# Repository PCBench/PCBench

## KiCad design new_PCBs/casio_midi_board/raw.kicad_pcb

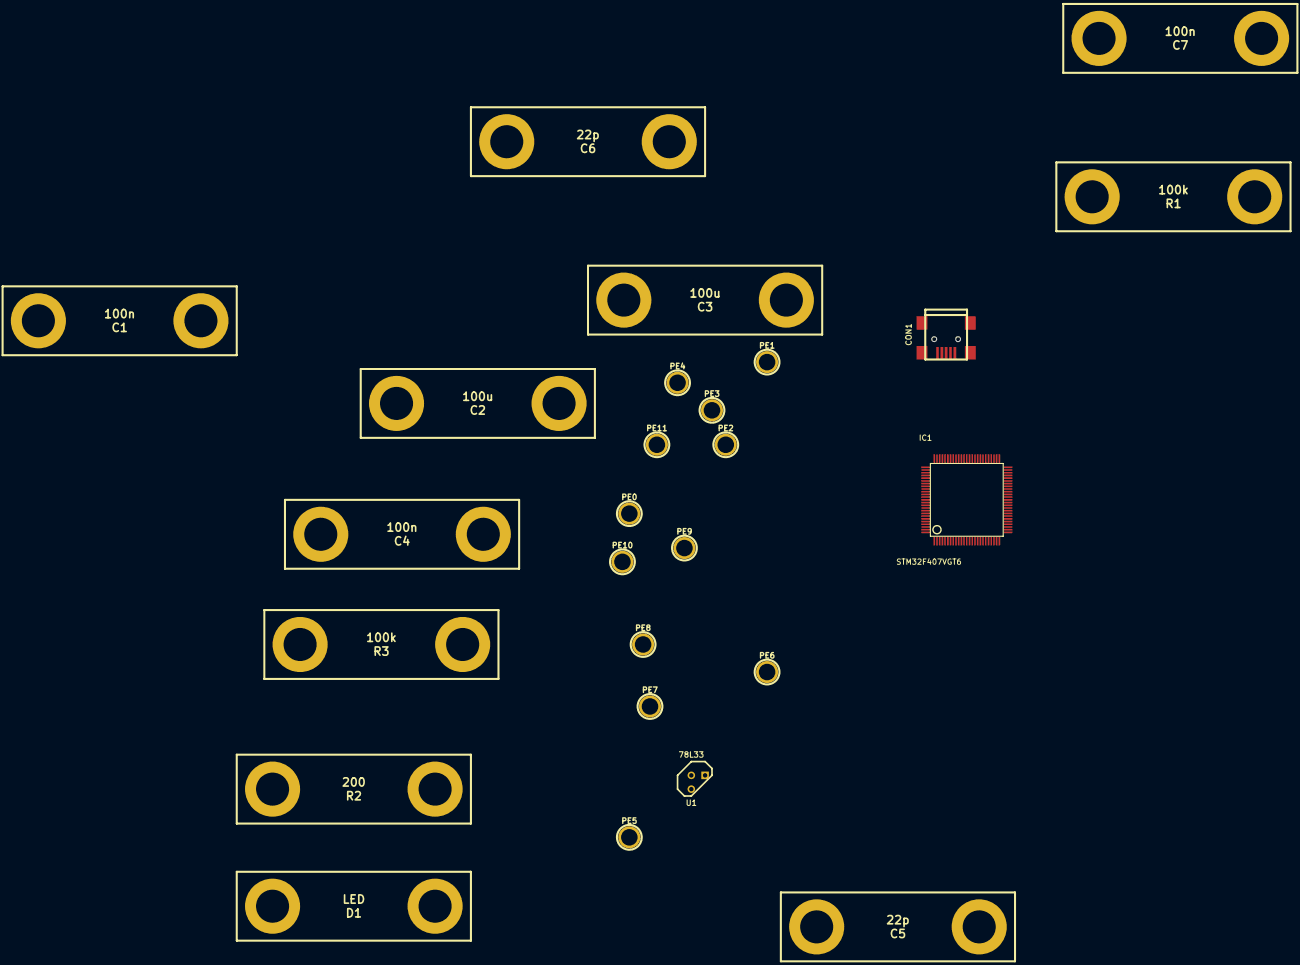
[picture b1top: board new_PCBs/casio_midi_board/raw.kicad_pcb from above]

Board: 2 copper layers, 26 parts (0 on the bottom side), 24 nets, no tracks yet.

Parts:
C1, C4, C7: 100n; 2PIN_6mm
C2, C3: 100u; 2PIN_6mm
C5, C6: 22p; 2PIN_6mm
CON1: USB-MINI-B; USB_MINI_B
D1: LED; 2PIN_6mm
IC1: STM32F407VGT6; QFP50P1600X1600X160-100N
PE0, PE1, PE2, PE3, PE4, PE5, PE6, PE7, PE8, PE9, PE10, PE11: CONN_1; 1pin
R1, R3: 100k; 2PIN_6mm
R2: 200; 2PIN_6mm
U1: 78L33; TO92

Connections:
GND: C1.2, C2.2, C3.2, C4.2, C5.2, C6.2, C7.2, CON1.5, D1.2, R3.2
unnamed: IC1.1, PE2.1
unnamed: IC1.23, R2.1
unnamed: D1.1, R2.2
unnamed: IC1.97, PE0.1
unnamed: IC1.98, PE1.1
unnamed: IC1.2, PE3.1
unnamed: IC1.3, PE4.1
unnamed: IC1.4, PE5.1
unnamed: IC1.5, PE6.1
unnamed: IC1.38, PE7.1
unnamed: IC1.39, PE8.1
unnamed: IC1.40, PE9.1
unnamed: IC1.41, PE10.1
unnamed: IC1.42, PE11.1
unnamed: C6.1, IC1.82
unnamed: C5.1, IC1.81
unnamed: C7.1, IC1.14, R1.1
unnamed: IC1.94, R3.1
unnamed: C1.1, C2.1, CON1.1
unnamed: C3.1, C4.1, IC1.6, IC1.11, IC1.19, IC1.28, IC1.50, IC1.75, IC1.100
unnamed: IC1.10, IC1.27, IC1.74, IC1.99
USB_DM: CON1.2, IC1.70
USB_DP: CON1.3, IC1.71

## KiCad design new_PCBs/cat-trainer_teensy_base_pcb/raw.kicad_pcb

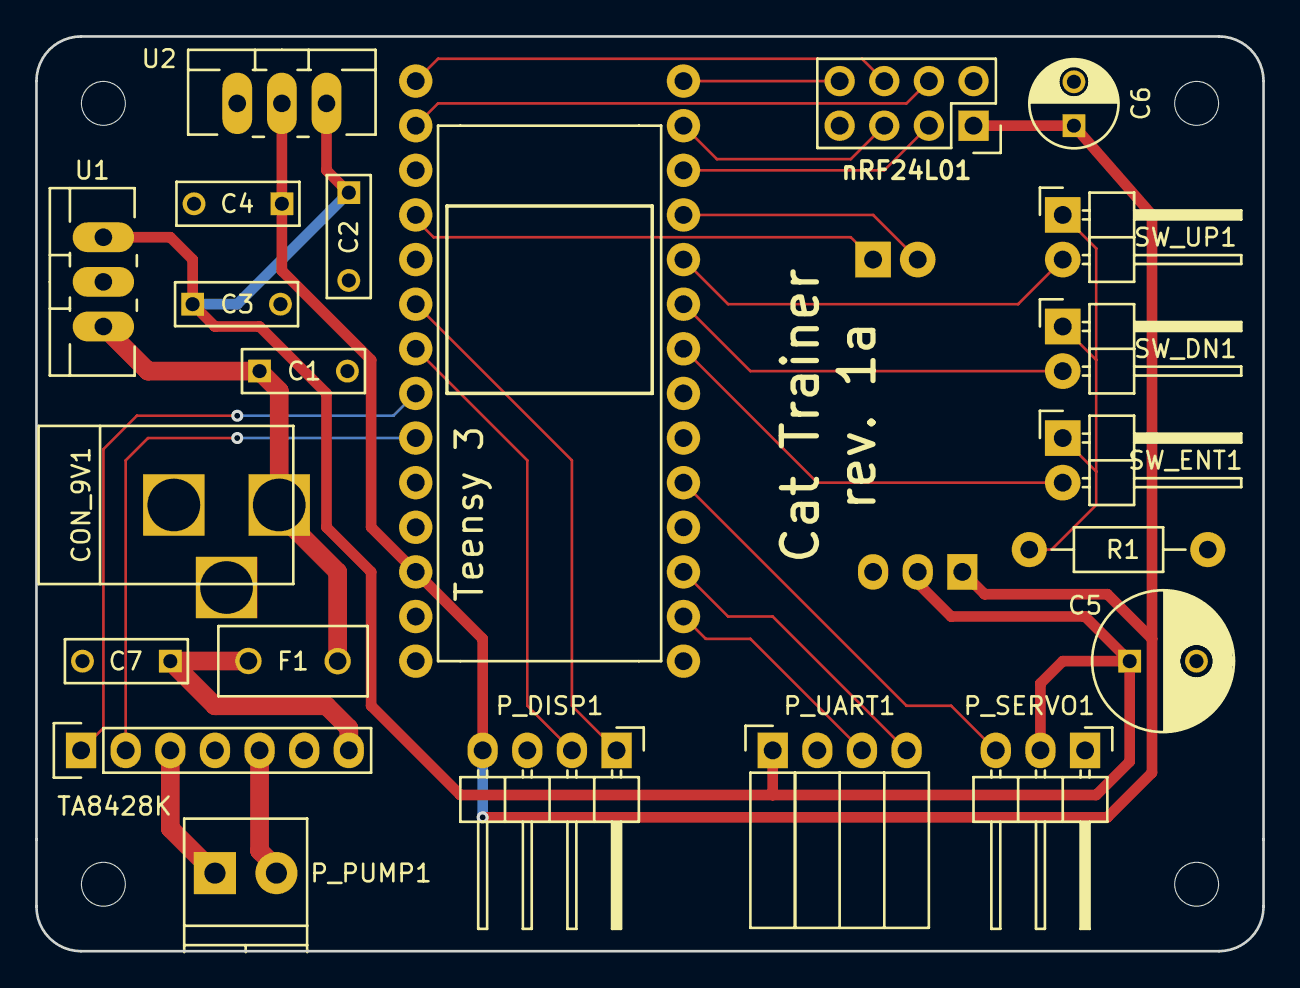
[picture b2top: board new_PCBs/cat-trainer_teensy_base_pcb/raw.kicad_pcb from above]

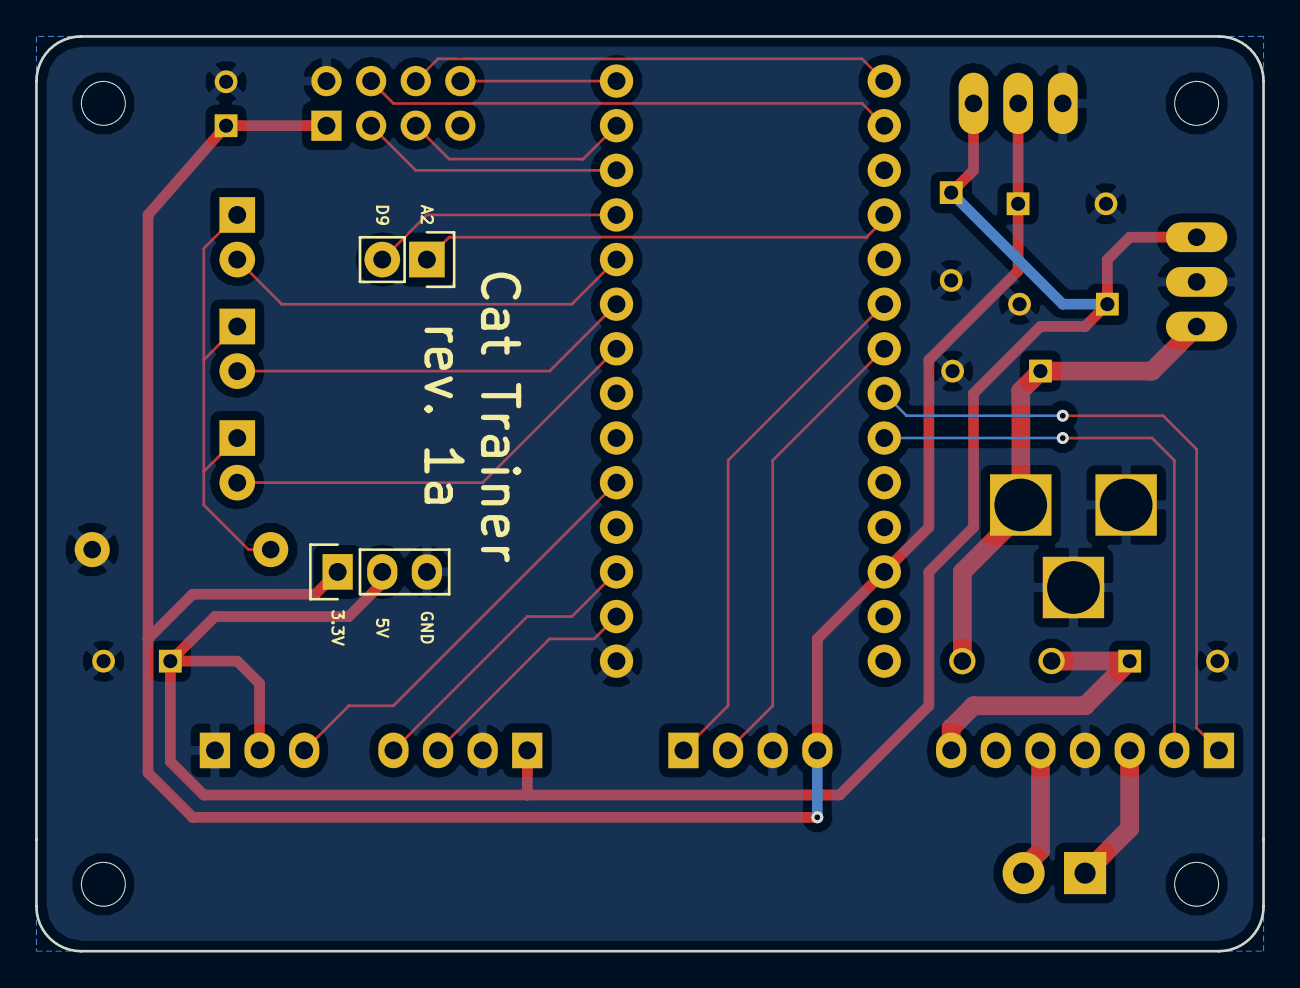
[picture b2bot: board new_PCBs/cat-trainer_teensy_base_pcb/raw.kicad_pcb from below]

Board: 2 copper layers, 69.9 x 52.1 mm, 24 parts (2 on the bottom side), 26 nets.

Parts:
C1: 330nF; C_Rect_L7_W2.5_P5
C2, C3: 100nF; C_Rect_L7_W2.5_P5
C4, C7: 10uF; C_Rect_L7_W2.5_P5
C5: 470uF; C_Radial_D8_L13_P3.8
C6: 100uF; C_Radial_D5_L11_P2.5
CON_9V1: BARREL_JACK
F1: F_Small; Fuse_TE5_Littlefuse-395Series
P_ACC1: CONN_01X03; Pin_Header_Straight_1x03
P_ACC2: CONN_01X02; Pin_Header_Straight_1x02
P_DISP1: CONN_01X04; Pin_Header_Angled_1x04
P_PUMP1: CONN_01X02; TerminalBlock_Pheonix_PT-3.5mm_2pol
P_SERVO1: CONN_01X03; Pin_Header_Angled_1x03
P_UART1: CONN_01X04; Socket_Strip_Angled_1x04
R1: 100; Resistor_Horizontal_RM10mm
SW_DN1: SW_PUSH; Pin_Header_Angled_1x02
SW_ENT1: SW_PUSH; Pin_Header_Angled_1x02
SW_UP1: SW_PUSH; Pin_Header_Angled_1x02
U1: LM7805CT; TO-220_Neutral123_Vertical_LargePads
U2: LD1117V33; TO-220_Neutral123_Vertical_LargePads
U3: Teensy_3.2; Teensy-3.1
U4: nRF24L01+; Socket_Strip_Straight_2x04
U5: TA8428K; Socket_Strip_Straight_1x07

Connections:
+3.3V: C4.1, C6.1, P_ACC1.1, P_DISP1.4, U2.2, U3.24, U4.2
+5V: C2.1, C3.1, C5.1, P_ACC1.2, P_SERVO1.2, P_UART1.1, U1.3, U2.3
+9V: C1.1, CON_9V1.1, F1.1, U1.1
ACC1: P_ACC2.2, U3.9
ACC2: P_ACC2.1, U3.16
GND: C1.2, C2.2, C3.2, C4.2, C5.2, C6.2, C7.2, CON_9V1.2, CON_9V1.3, P_ACC1.3, P_DISP1.3, P_SERVO1.1, P_UART1.2, R1.2, U1.2, U2.1, U3.27, U4.1, U5.4
NC: U3.2, U3.4, U3.5, U3.15, U3.17, U3.22, U3.23, U3.25, U3.26, U4.8
unnamed: C7.1, F1.2, U5.7
unnamed: P_DISP1.1, U3.18
unnamed: P_DISP1.2, U3.19
unnamed: P_PUMP1.1, U5.3
unnamed: P_PUMP1.2, U5.5
unnamed: P_SERVO1.3, U3.3
unnamed: P_UART1.3, U3.0
unnamed: P_UART1.4, U3.1
unnamed: R1.1, SW_DN1.1, SW_ENT1.1, SW_UP1.1
unnamed: SW_DN1.2, U3.7
unnamed: SW_ENT1.2, U3.6
unnamed: SW_UP1.2, U3.8
unnamed: U3.10, U4.4
unnamed: U3.11, U4.6
unnamed: U3.12, U4.7
unnamed: U3.13, U4.5
unnamed: U3.14, U4.3
unnamed: U3.20, U5.1
unnamed: U3.21, U5.2

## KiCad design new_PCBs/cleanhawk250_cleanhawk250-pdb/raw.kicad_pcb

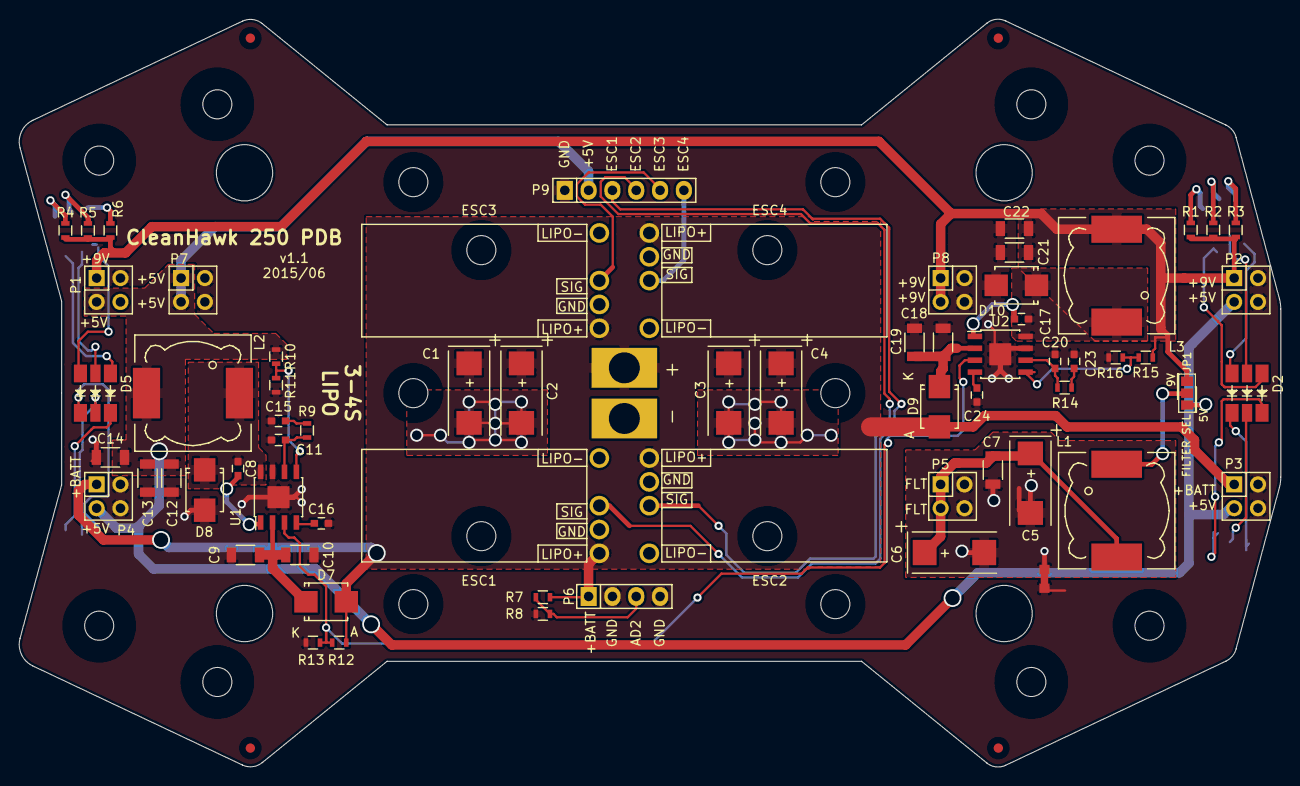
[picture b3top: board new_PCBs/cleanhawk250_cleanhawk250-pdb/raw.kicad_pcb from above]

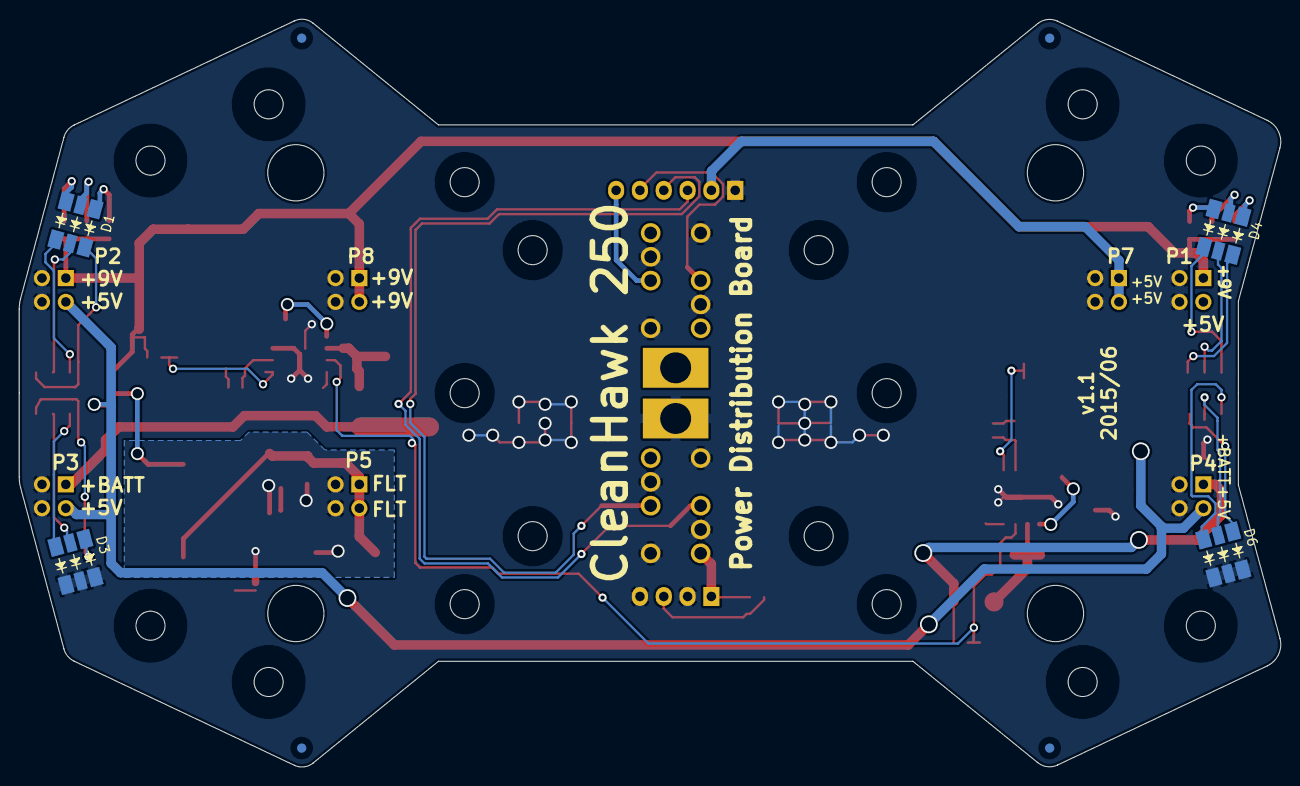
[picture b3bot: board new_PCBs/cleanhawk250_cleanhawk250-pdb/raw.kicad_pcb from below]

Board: 2 copper layers, 134.5 x 79.7 mm, 80 parts (8 on the bottom side), 45 nets.

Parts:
C1, C2, C3, C4: 33uF/25V/np; TantalC_SizeD_EIA-7343_Reflow
C5, C6: 100uF/16V; TantalC_SizeD_EIA-7343_Reflow
C7, C9, C10, C18, C19: 10uF/35V; C_1206
C8, C17: 100nF; C_0603
C11, C20: 18pF; C_0603
C12, C13, C14: 22uF/10V; C_1206
C15, C23: 680pF; C_0603
C16, C24: 8.2nF; C_0603
C21, C22: 22uF/16V; C_1206
D1, D2, D3, D4, D5, D6: RGB_LED_5050; LED_5050_RGB
D7, D8, D9, D10: B340LB; Diode-SMB_Standard
ESC1, ESC2, ESC3, ESC4: KISS_ESC_18A; Kiss_ESC_18A_v1.1
F1, F2, F3, F4, F5, F6, F7, F8: SPECIAL; FIDUCIAL_1MM
FRAME1: SPECIAL; Emax250_Bottom_Holes
JP1: FILTER SEL; AB2_SJMP_03-1
JP2: JUMPER; NetTie-I_Connected_SMD
L1: 820uH; Choke_SMD_12x12mm_h6mm
L2, L3: 8.2uH; Choke_SMD_12x12mm_h6mm
P1, P2, P3, P4, P5, P7, P8: CONN_02X02; Pin_Header_Straight_2x02
P6: CONN_01X04; Pin_Header_Straight_1x04
P9: CONN_01X06; Pin_Header_Straight_1x06
R1, R3: 68; R_0603
R2, R5: 120; R_0603
R4, R6: 68/np; R_0603
R7, R10, R15: 10k/1%; R_0603
R8: 2.32k/1%; R_0603
R9, R14: 78.7k; R_0603
R11: 1.91k/1%; R_0603
R12: 169k/np; R_0603
R13: 28k/np; R_0603
R16: 976/1%; R_0603
U1, U2: TPS54331; SOIC-8-1EP_3.9x4.9mm_Pitch1.27mm
W1: WIREPADS; WirePads_12AWG_TH

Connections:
+5V: C12.1, C13.1, C14.1, JP1.3, L2.2, P1.3, P2.3, P3.3, P4.3, P7.1, P7.3, P9.2, R10.1
+9V: C21.1, C22.1, JP1.1, L3.2, P1.1, P2.1, P8.1, P8.3, R1.2, R2.2, R3.2, R4.2, R5.2, R6.2, R15.1
+BATT: C1.1, C2.1, C3.1, C4.1, D7.2, D9.2, ESC1.1, ESC2.1, ESC3.1, ESC4.1, P3.1, P4.1, P6.1, R7.2, R12.1, W1.+
ESC1: ESC1.2, P9.3
ESC2: ESC2.2, P9.4
ESC3: ESC3.2, P9.5
ESC4: ESC4.2, P9.6
GND: C1.2, C2.2, C3.2, C4.2, C9.2, C10.2, C11.2, C12.2, C13.2, C14.2, C15.2, C16.2, C18.2, C19.2, C20.2, C21.2, C22.2, C23.2, C24.2, D3.4, D3.5, D3.6, D6.4, D6.5, D6.6, D8.2, D10.2, ESC1.3, ESC1.4, ESC2.3, ESC2.4, ESC3.3, ESC3.4, ESC4.3, ESC4.4, JP2.1, P1.2, P1.4, P2.2, P2.4, P3.2, P3.4, P4.2, P4.4, P6.2, P6.4, P7.2, P7.4, P8.2, P8.4, P9.1, R8.2, R11.2, R13.2, R16.2, U1.7, U1.9, U2.7, U2.9, W1.-
GNDA: C5.2, C6.2, C7.2, JP2.2, P5.2, P5.4
unnamed: C5.1, C6.1, C7.1, L1.2, P5.1, P5.3
unnamed: C8.1, U1.1
unnamed: C8.2, D8.1, L2.1, U1.8
unnamed: C9.1, C10.1, D7.1, U1.2
unnamed: C11.1, R9.1, U1.6
unnamed: C15.1, R9.2
unnamed: C16.1, U1.4
unnamed: C17.1, U2.1
unnamed: C17.2, D10.1, L3.1, U2.8
unnamed: C18.1, C19.1, D9.1, U2.2
unnamed: C20.1, R14.1, U2.6
unnamed: C23.1, R14.2
unnamed: C24.1, U2.4
unnamed: D1.1, R1.1
unnamed: D1.2, R2.1
unnamed: D1.3, R3.1
unnamed: D1.4, D2.3
unnamed: D1.5, D2.2
unnamed: D1.6, D2.1
unnamed: D2.4, D3.3
unnamed: D2.5, D3.2
unnamed: D2.6, D3.1
unnamed: D4.1, R4.1
unnamed: D4.2, R5.1
unnamed: D4.3, R6.1
unnamed: D4.4, D5.3
unnamed: D4.5, D5.2
unnamed: D4.6, D5.1
unnamed: D5.4, D6.3
unnamed: D5.5, D6.2
unnamed: D5.6, D6.1
unnamed: JP1.2, L1.1
unnamed: P6.3, R7.1, R8.1
unnamed: R10.2, R11.1, U1.5
unnamed: R15.2, R16.1, U2.5
REG_EN: R12.2, R13.1, U1.3, U2.3

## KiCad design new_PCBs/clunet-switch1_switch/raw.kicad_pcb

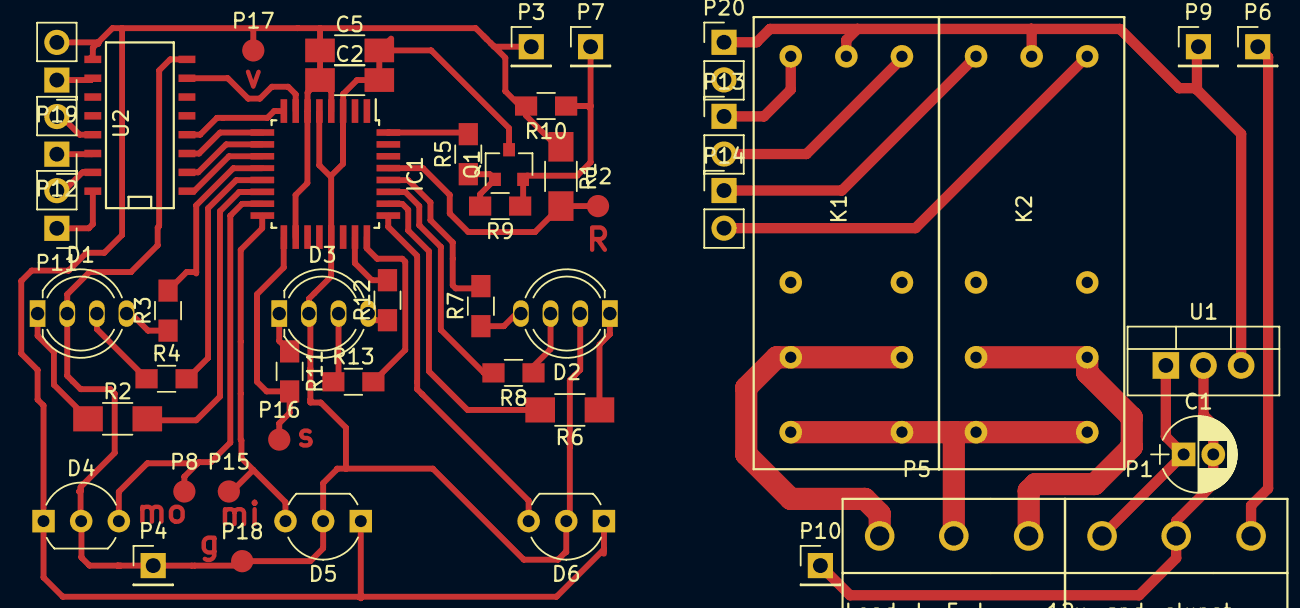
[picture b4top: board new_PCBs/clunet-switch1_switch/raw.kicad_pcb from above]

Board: 2 copper layers, 48 parts (0 on the bottom side), 48 nets.

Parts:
C1: 100mkf; CP_Radial_D5.0mm_P2.00mm
C2: 10mkf; C_1206_HandSoldering
C5: C_Small; C_1206_HandSoldering
D1, D2, D3: Led1; LED_D5.0mm-4-LL
D4, D5, D6: AH201; TO-92_Inline_Wide
IC1: ATMEGA8A-A; TQFP-32_7x7mm_Pitch0.8mm-LUT
K1, K2: RT424F05
P1: 12v-gnd-clunet; DG301-5.0-3x
P2: Reset; Measurement_Point_Round-SMD-Pad_Small
P3, P9: Vcc; Socket_Strip_Straight_1x01_Pitch2.54mm
P4, P10: Gnd; Socket_Strip_Straight_1x01_Pitch2.54mm
P5: Load-L-F-L; DG301-5.0-3x
P6, P7: Clunet; Socket_Strip_Straight_1x01_Pitch2.54mm
P8: CON_MOS; Measurement_Point_Round-SMD-Pad_Small
P11, P13: R1_; Socket_Strip_Straight_1x02_Pitch2.54mm
P12, P14: R2_; Socket_Strip_Straight_1x02_Pitch2.54mm
P15: CON_MIS; Measurement_Point_Round-SMD-Pad_Small
P16: CON_SCK; Measurement_Point_Round-SMD-Pad_Small
P17: Vcc_Prog; Measurement_Point_Round-SMD-Pad_Small
P18: Gnd_Prog; Measurement_Point_Round-SMD-Pad_Small
P19, P20: SPK; Socket_Strip_Straight_1x02_Pitch2.54mm
Q1: PNP BC858; SOT-23
R1: 1.5K; R_1206_HandSoldering
R2, R6: 470R; R_1206_HandSoldering
R3, R4, R7, R8, R11, R12, R13: 470R; R_0805_HandSoldering
R5: 2.2K; R_0805_HandSoldering
R9: 22K; R_0805_HandSoldering
R10: 560R; R_0805_HandSoldering
U1: 7805; TO-220_Vertical-LM7805
U2: ULN2003-norm; SO-16-N

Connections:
+5V: K1.3, K2.3, P9.1, P20.1, U1.VO
+12V: C1.1, P1.1, U1.VI
/LED1_1: IC1.14, R2.2
/LED1_2: IC1.13, R4.2
/LED1_3: IC1.12, R3.2
/LED2_1: IC1.17, P16.1, R11.2
/LED2_2: IC1.23, R12.2
/LED2_3: IC1.24, R13.2
/LED3_1: IC1.26, R6.2
/LED3_2: IC1.27, R8.2
/LED3_3: IC1.28, R7.2
/R1_1: IC1.11, U2.1
/R1_2: IC1.10, U2.2
/R2_1: IC1.9, U2.3
/R2_2: IC1.8, U2.4
/SW1: D4.3, IC1.15, P8.1
/SW2: D5.3, IC1.16, P15.1
/SW3: D6.3, IC1.25
/spk: IC1.7, U2.7
GND: C2.2, C5.2, D1.2, D2.2, D3.2, D4.2, D5.2, D6.2, IC1.3, IC1.5, IC1.21, P4.1, P18.1, Q1.3, U2.8
GNDA: C1.2, P1.2, P10.1, U1.GND
unnamed: D1.1, R2.1
unnamed: D1.3, R4.1
unnamed: D1.4, R3.1
unnamed: D2.1, R6.1
unnamed: D2.3, R8.1
unnamed: D2.4, R7.1
unnamed: D3.1, R11.1
unnamed: D3.3, R13.1
unnamed: D3.4, R12.1
unnamed: IC1.29, P2.1, R1.2
unnamed: IC1.32, R5.2
unnamed: K1.1, P13.2
unnamed: K1.2, P13.1
unnamed: K1.11, K1.21, P5.1
unnamed: K1.14, K1.24, K2.14, K2.24, P5.2
unnamed: K2.1, P14.2
unnamed: K2.2, P14.1
unnamed: K2.11, K2.21, P5.3
unnamed: P1.3, P6.1
unnamed: P11.1, U2.16
unnamed: P11.2, U2.15
unnamed: P12.1, U2.14
unnamed: P12.2, U2.13
unnamed: P19.1, U2.10
unnamed: Q1.1, R5.1, R9.2
VCC: C2.1, C5.1, D4.1, D5.1, D6.1, IC1.4, IC1.6, IC1.18, P3.1, P17.1, P19.2, R1.1, R10.2, U2.9
clunet: P7.1, Q1.2, R9.1, R10.1

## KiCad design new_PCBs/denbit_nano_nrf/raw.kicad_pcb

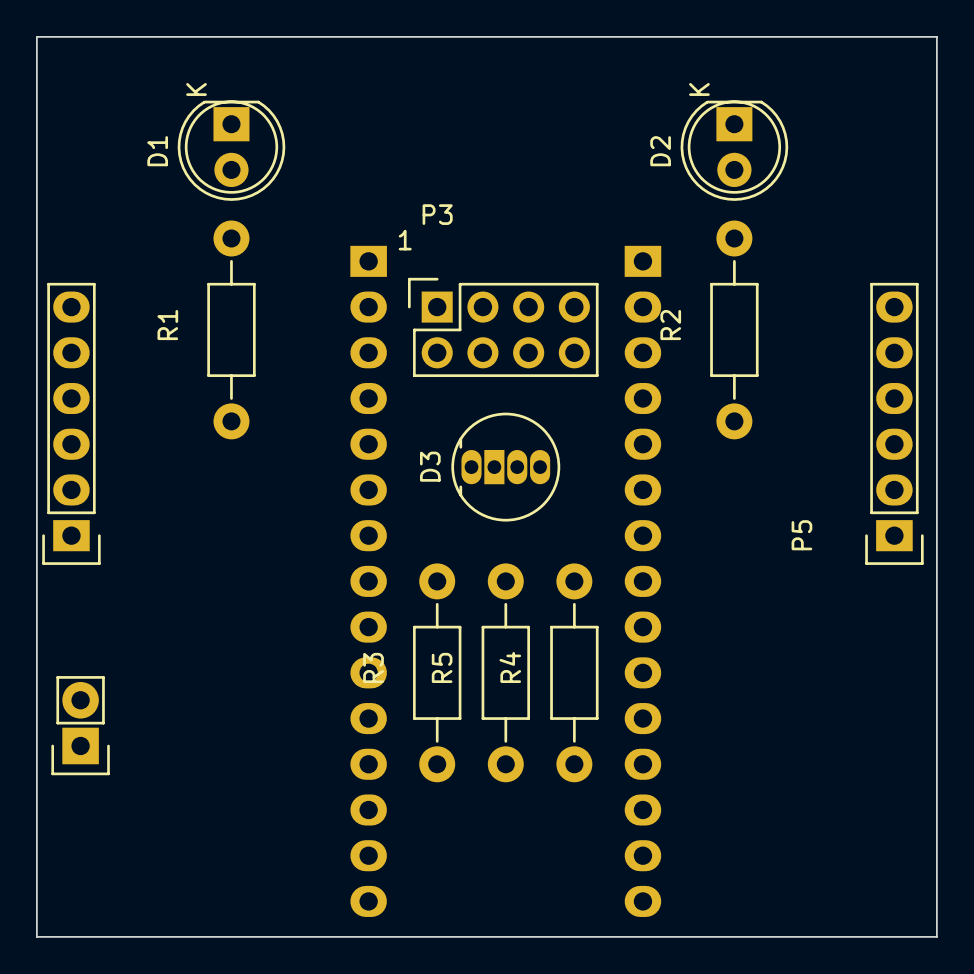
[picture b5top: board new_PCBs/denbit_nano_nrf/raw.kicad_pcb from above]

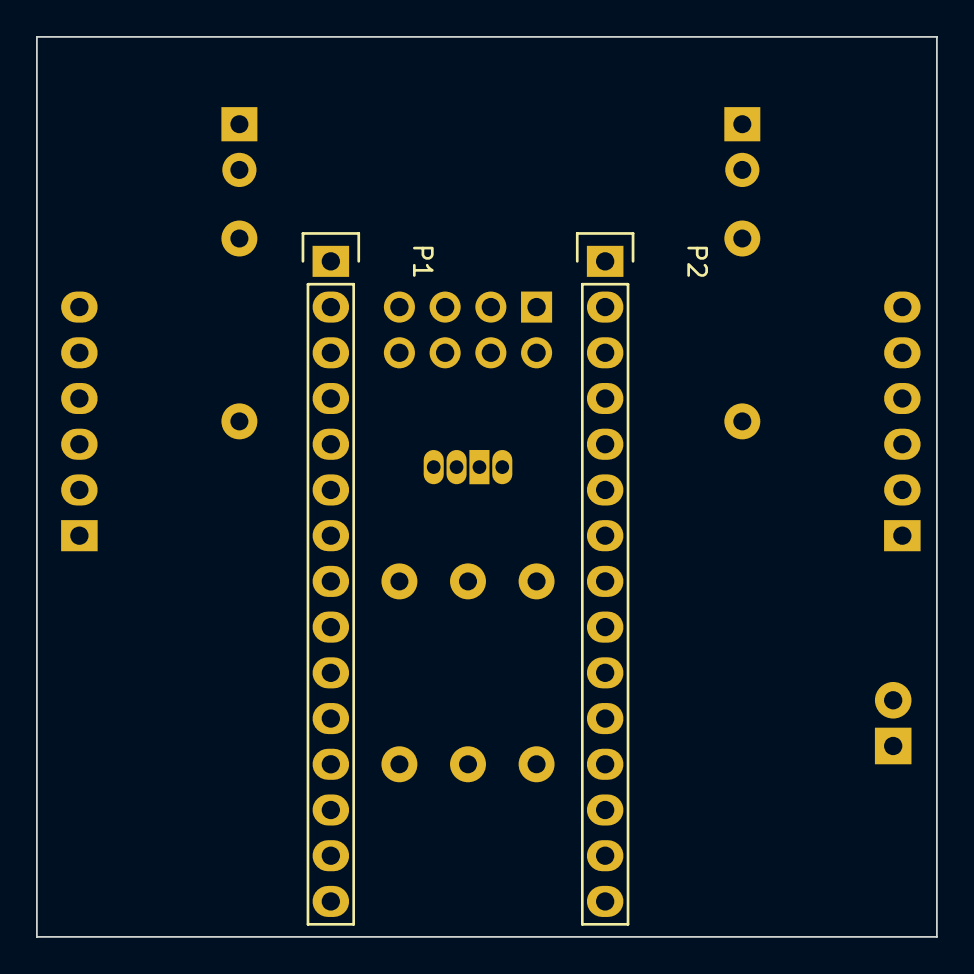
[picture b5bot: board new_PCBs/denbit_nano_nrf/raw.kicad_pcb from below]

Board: 2 copper layers, 50.0 x 50.0 mm, 15 parts (2 on the bottom side), 21 nets, no tracks yet.

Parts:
D1, D2: LED; LED-5MM
D3: LED_RCBG; LED-RGB-5MM_Common_Cathode
P1: Digital; Socket_Strip_Straight_1x15
P2: Analog; Socket_Strip_Straight_1x15
P3: CONN_02X04; Socket_Strip_Straight_2x04
P4, P5: CONN_01X06; Socket_Strip_Straight_1x06
P6: CONN_01X02; 1pin_Nano
P10: CONN_01X02; Socket_Strip_Straight_1x02
R1, R2, R4, R5: 100R; Resistor_Horizontal_RM10mm
R3: 180R; Resistor_Horizontal_RM10mm

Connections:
/3: P1.6, R3.1
/3V3: P2.14, P3.2, P4.2, P5.2
/5: P1.8, R4.1
/5V: P2.4, P10.2
/6: P1.9, R5.1
/8: P1.11, P3.4, R2.1
/9: P1.12, R1.1
/10(SS): P1.13, P5.6
/11(MOSI): P1.14, P3.6, P5.5
/12(MISO): P1.15, P3.7, P5.4
/13(SCK): P2.15, P3.5, P5.3
/A0: P2.12, P4.6
/A1: P2.11, P4.5
/A4(SDA): P2.8, P4.4
/A5(SCL): P2.7, P4.3
/LED_GREEN: D2.2, R2.2
/LED_RED: D1.2, R1.2
/RGB_BLUE: D3.3, R5.2
/RGB_GREEN: D3.4, R4.2
/RGB_RED: D3.1, R3.2
GND: D1.1, D2.1, D3.2, P1.4, P2.2, P3.1, P4.1, P5.1, P10.1

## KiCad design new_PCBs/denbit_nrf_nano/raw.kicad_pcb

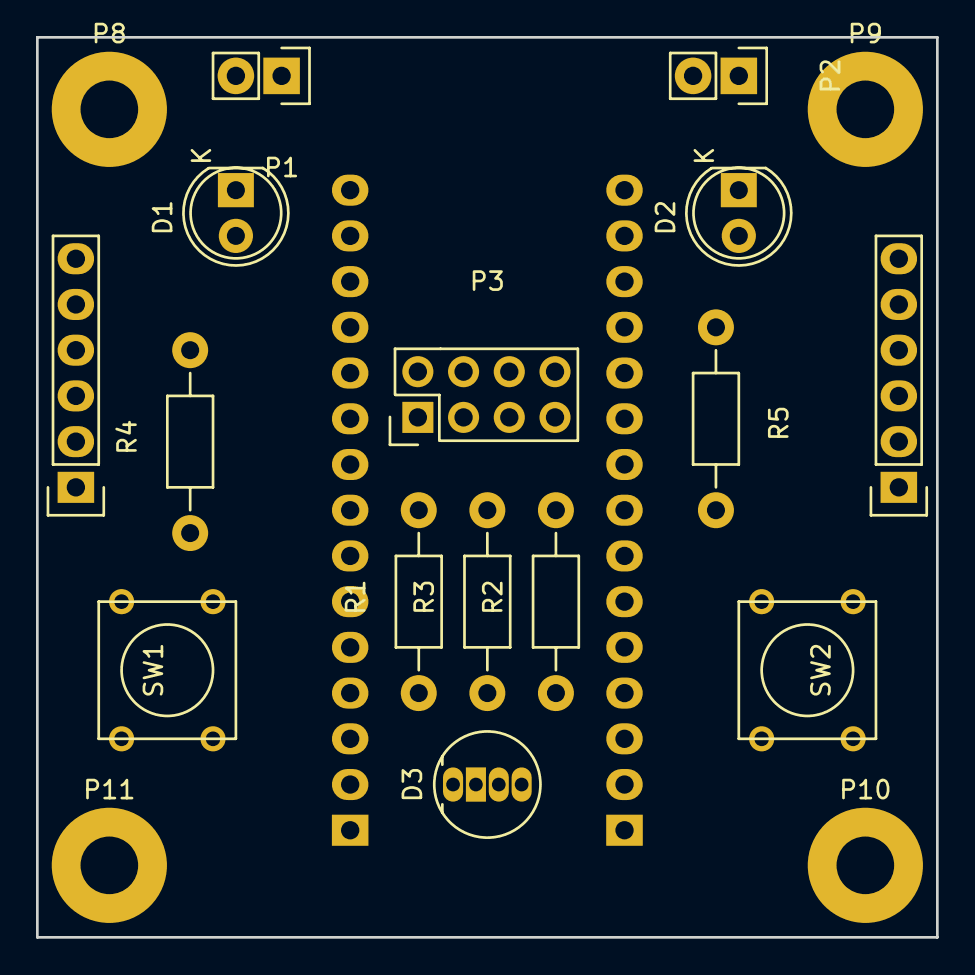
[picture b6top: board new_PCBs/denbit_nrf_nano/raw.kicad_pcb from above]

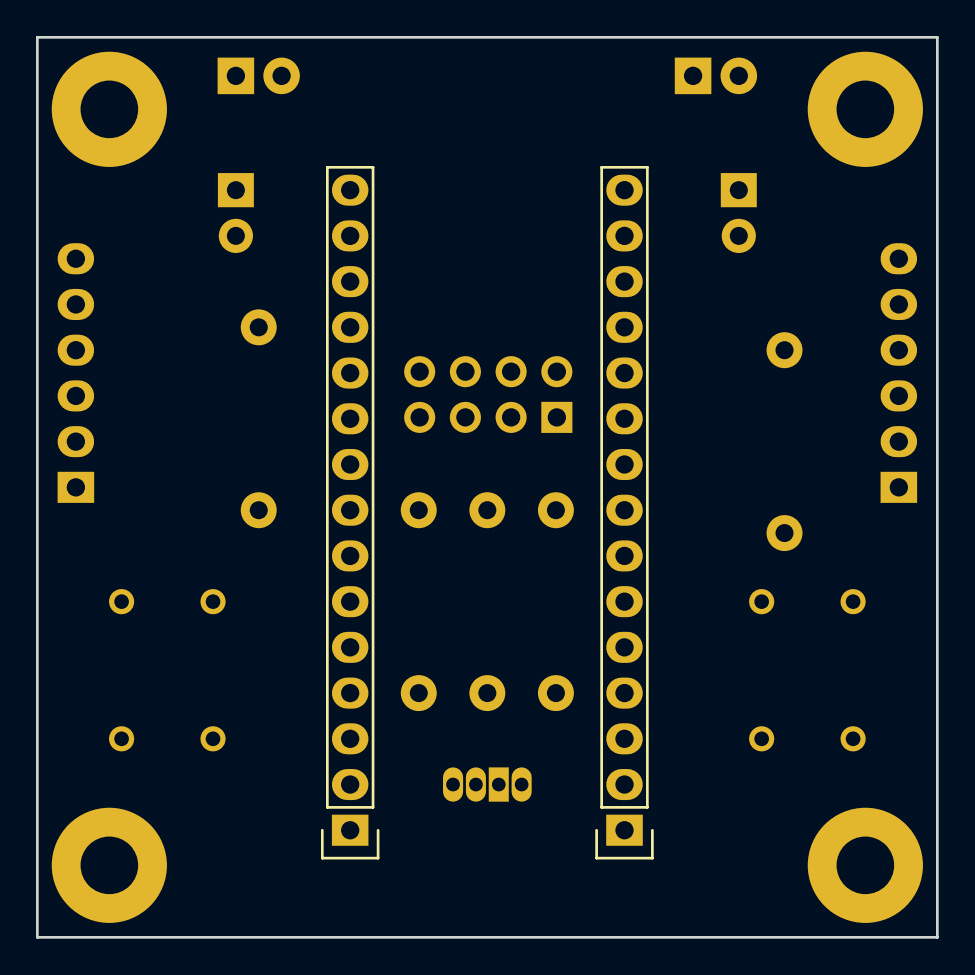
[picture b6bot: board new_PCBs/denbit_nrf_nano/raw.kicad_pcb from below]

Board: 2 copper layers, 50.0 x 50.0 mm, 21 parts (2 on the bottom side), 25 nets, no tracks yet.

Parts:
D1, D2: LED; LED-5MM
D3: LED_RCBG; LED-RGB-5MM_Common_Cathode
P1: 5V_OUT; Socket_Strip_Straight_1x02
P2: ALT_PWR; Pin_Header_Straight_1x02
P3: NRF_24L01
P4, P6: CONN_01X15; Socket_Strip_Straight_1x15
P5, P7: CONN_01X06; Socket_Strip_Straight_1x06
P8, P9, P10, P11: MOUNT_HOLE; MountingHole_3.2mm_M3_Pad
R1: 180R; Resistor_Horizontal_RM10mm
R2, R3, R4, R5: 100R; Resistor_Horizontal_RM10mm
SW1, SW2: SW_PUSH; SW_PUSH_SMALL

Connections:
3V3: P3.2, P5.2, P6.2
5V: P1.2, P6.12, P7.2
/LED_GREEN: D1.2, R4.1
/LED_RED: D2.2, R5.1
ADC0: P5.6, P6.4
ADC1: P5.5, P6.5
D2: P4.11, SW1.2
D3: P4.10, R1.2
D4: P4.9, R4.2
D5: P4.8, R5.2
D6: P4.7, R2.2
D7: P3.3, P4.6, SW2.2
D8: P3.4, P4.5
D9: P4.4, R3.2
GND: D1.1, D2.1, D3.2, P1.1, P2.1, P3.1, P4.12, P5.1, P6.14, P7.1, P8.1, P9.1, P10.1, P11.1, SW1.1, SW2.1
MISO: P3.7, P4.1, P7.4
MOSI: P3.6, P4.2, P7.5
unnamed: D3.1, R1.1
unnamed: D3.3, R3.1
unnamed: D3.4, R2.1
SCK: P3.5, P6.1, P7.3
SCL: P5.3, P6.9
SDA: P5.4, P6.8
SS: P4.3, P7.6
VIN: P2.2, P6.15
